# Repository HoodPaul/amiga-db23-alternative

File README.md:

# Amiga DB23 Video and Floppy Adapter

An adapter assembly for the Amiga's motherboard-mounted **DB23 RGB video and external floppy connectors**. A genuine solder-cup DB23 joins a small horizontal PCB, 23 supported straight pins and a solid printed base. Two screws clamp the assembly through the original motherboard mounting holes, with nuts above the adapter PCB and insulating washers under the motherboard-side heads. An optional cosmetic cover locates on the front towers and can be secured with tiny glue spots. **Mechanical/assembly revision: 0.6. PCB revision: 0.5.**

Project development: **Paul of UK Computing Limited**, **Jon of JMC Electronics** and **AI assistance through Codex**. This develops Paul's supplied straddle-PCB concept and supported loose-pin construction.

Repository: [HoodPaul/amiga-db23-alternative](https://github.com/HoodPaul/amiga-db23-alternative).

**Status, 30 October 2026: fit prototype. Paul has trial-printed revision 0.5 and reported delicate lid projections and nuts contained within the print footprint. The revised 0.6 parts have not yet been printed. The complete connector, fastener and PCB stack remains unmeasured. No physical strength, assembled electrical operation or Amiga compatibility test has been completed.** Native files and trial prints make those checks possible; this is not a production release.

For engineering or AI work, read [AGENTS.md](AGENTS.md), the [handover](docs/AI-HANDOVER.md) and [documentation index](docs/README.md).

The printed geometry comes from the delivered CAD. Bought connector bodies, cups, pins and hardware are unmeasured reference envelopes. Their appearance does not prove a purchased part fits. See the [drawing PDF](previews/DB23_Prototype_Drawings_v0.6.pdf) for fit references and assembly views.

## Revision 0.6 mechanical arrangement

The DB23 cups straddle the front of the PCB: contacts 1–12 solder to the top and 13–23 to the bottom. Twenty-three separate pins pass through the base into the original motherboard signal holes.

The PCB has side ears with plated `SHIELD` mounting lands at the original shell-anchor positions. **M3 screws enter from underneath the motherboard**, pass through the solid base and PCB, and take nuts on top, with insulating washers beneath the screw heads. The printed base has one broad, flat underside at motherboard Z0 and supports the PCB at Z5.75.

The forward towers have straight, square outer faces at X±25.60. Clearance for neighbouring components starts behind the towers.

Dedicated J4 shell-bond pads keep wire and solder away from the J3 nut-bearing lands. The cap fits last, after mounting and inspection. It provides the discreet black appearance; fitted jackposts must retain their nuts with the cover absent. The solid base and through-bolts carry the intended cable loads. Actual insertion strength and clamping behaviour remain untested.

The build order follows four parts: **join DB23 and PCB; load pins with the separate height jig and solder the joined assembly onto them; fit jackpost nuts and posts; mount and solder to the motherboard, inspect, then fit the cap.** See the [assembly guide](docs/ASSEMBLY.md).

## PCB variants

Open the matching project with **KiCad 7.0 or newer**:

| Variant | Native project | Connector on the Amiga |
|---|---|---|
| RGB video | [DB23M_RGB.kicad_pro](pcb/DB23M_RGB/DB23M_RGB.kicad_pro) | Male DB23 solder-cup connector |
| External floppy | [DB23F_Floppy.kicad_pro](pcb/DB23F_Floppy/DB23F_Floppy.kicad_pro) | Female DB23 solder-cup connector |

Local symbols and footprints are included. Male and female pin numbering is mirrored; use the matching PCB.

| PCB property | Revision 0.5 |
|---|---|
| Overall board envelope | **51.20 × 9.00 mm**, Y4.00–13.00, with mounting ears, front clearance steps and local reliefs |
| Layers / assumed thickness | **Two / 1.00 mm**; confirm the actual cup gap |
| Proposed finish | Black mask, white silkscreen, ENIG exposed pads |
| PCB legend, both faces | **Amiga DB23 REV 0.5**, nominal 0.70 mm text height / 0.10 mm stroke |
| Signal track / clearance | **0.50 / 0.20 mm** |
| Tail drill / pad | **1.04 / 1.70 mm** |
| J3 mounting drill / pad | **3.30 / 6.50 mm** |
| J4 shell-wire drill / pad | **1.20 / 2.40 mm** |
| Along-row pitch / spacing / stagger | **2.77 / 2.84 / 1.385 mm** |
| Front / rear signal rows | **Y8.08 / Y10.92 mm** from flange datum |
| Shell mounting centres | **44.27 mm**, at **Y9.50 mm** |
| Nominal mating centreline | **6.25 mm** above the motherboard |

The hole pattern and mating references are nominal values from the [iComp OEM-equivalent drawings](docs/SOURCES.md). The PCB rear is now Y13.00 rather than Y16.00, 3.00 mm shorter than revision 0.4. The cap reaches Y13.20, 0.70 mm behind the OEM reference rear at Y12.50. The prints are 52.00 mm wide, but the pair of Ø8 underside washers spans 52.27 mm. Actual side-exiting wire and case/component clearance still need checking on the target motherboard.

## Printed parts and mounting hardware

The [mechanical folder](mechanical/) contains editable OpenSCAD and the following trial parts:

- [Solid base STL](mechanical/DB23_Holder_v0.6.stl) and [STEP](mechanical/DB23_Holder_v0.6.step).
- [Optional cover STL](mechanical/DB23_Cap_v0.6.stl) and [STEP](mechanical/DB23_Cap_v0.6.step).
- [Pin-height jig](mechanical/DB23_Pin_Height_Jig_v0.6.stl) and [hole-fit coupon](mechanical/DB23_Hole_Fit_Coupon_v0.6.stl).

Read [mechanical notes](docs/MECHANICAL.md) and `mechanical/MECHANICAL_NOTES.txt` for orientations and fit allowances. The cap STL is already roof-down for printing; its STEP uses assembly coordinates. The base has a broad, flat Z0 underside for direct bed placement, subject to the usual first-layer and dimensional trial.

All 23 guides now have **0.40 mm deep, 45° entry funnels**, opening to **Ø1.72 mm** at the surface. This is two layers at 0.20 mm layer height, with the straight retaining bore preserved below. The cover has a **1.60 mm roof**, a short **1.20 mm rim**, and two broad locating tabs. The four thin projections, two hooks and their base catches are removed; obsolete clip coupons are removed too.

The default guides are nominally **Ø0.92 mm** for assumed **0.64 mm square pins**. Their diagonal is about **0.905 mm**, so a finished Ø0.80 mm round bore is too small. Establish snug pin retention using the coupon and actual pins. Use the funnel to guide careful hand clearing with a pin vice if needed. Hot insertion is unvalidated and can move or soften the guide. The loading jig sets a common lower-tip stop; equal upper heights also need equal pin lengths. Remove the jig before soldering.

The default motherboard fastener is **M3 × 12 mm under-head length**, with a user-listed **Ø7 mm, approximately 1 mm thick head**. Fit a **Ø8 mm insulating washer, assumed 0.50 mm thick, beneath each head**; the top nut bears directly on its supported J3 land. With an assumed 1.60 mm motherboard and 2.40 mm nut, the stack takes 11.25 mm, leaving 0.75 mm beyond the nut. The screw tip is Z9.90 and the head bottom Z−3.10, 1.50 mm beneath the assumed motherboard underside. Measure the real stack and underside/chassis clearance. **14 and 16 mm screws require trimming or separately checked cap clearance.** A top washer is not part of the default stack and needs a separate length check. No motherboard countersinking or drilling is specified.

Port jackposts need **4-40 UNC cable-facing threads** and rear stems matching the captive nuts. Prototype defaults use M3 rear stems and nuts. The clearance passage ends at Y6.20; the conservative permitted stem end is **Y≤6.00 from the flange datum**, before the upward mounting nuts. Select the actual hardware before freezing the print.

## Electrical arrangement and validation

All **23 positions pass independently, pin n to pin n**, using neutral `P01`–`P23` names. The bare PCB keeps `SHIELD` separate from every signal pin, including video pin 13. It adds no buffering, conversion, protection or change to the Amiga interface.

J3 mounting lands and J4 shell-wire pads share `SHIELD`. Provide deliberate wires or metal bonds from the DB23 shell and from J4 to the original motherboard shell-ground pad. The default head washers are insulating, and mounting-bolt contact is not relied upon for motherboard grounding. Plastic provides no grounding.

Use the [current validation record](docs/VALIDATION.md) for actual native DRC, exact-netlist and independent geometry results. Native schematic ERC is not claimed. CAD checks do not establish physical fit, printed strength, heat tolerance or working hardware.

Run the portable PCB audit from the project root:

```sh
python3 source/verify_pcb.py
```

Complete the [measurements](docs/MEASUREMENTS.md) and trial prints before a board order. Generated files under [fabrication/FIT-PROTOTYPE/](fabrication/FIT-PROTOTYPE/) are coordinated prototype exports, not a measured production release.

## Project contents

| Path | Purpose |
|---|---|
| [pcb/](pcb/) | Both KiCad projects and local libraries |
| [mechanical/](mechanical/) | Editable source, print trials and STEP geometry |
| [previews/](previews/) | Assembly, print and PCB views, drawing PDF |
| [docs/](docs/) | Assembly, measurements, design decisions and handover |
| [source/](source/) | Shared parameters, builders and verifiers |
| [verification/](verification/) | Actual native and saved-file reports |
| [BOM.csv](BOM.csv) | Parts and selection assumptions |
| [CHANGELOG.md](CHANGELOG.md) | Revision history |
| [NOTICE.md](NOTICE.md) | Project and third-party notices |

## Universal PCB prototype — ordered 30 October 2026

**Use the universal PCB at your own risk.** A separate [universal prototype package](pcb/DB23_Universal_Prototype/README.md) now includes editable PCB, Gerbers/drills, preview, checks and order records. It retains the existing physical routing, adds VIDEO 1 / FLOPPY 1 markings on both faces, removes other numbers and uses round signal pads. Internal numbering remains the VIDEO reference; actual connector orientation and continuity must be checked.

Paul confirmed ordering 30 boards from JLCPCB on 30 October 2026: two-layer FR-4, 1.00 mm, 1 oz, black mask, white silkscreen, ENIG. Receipt, physical fit and functional operation remain unverified. Native KiCad 10.0.7 DRC reports zero errors/unconnected items and four missing-library warnings; exact checks confirm 23 separate signal connections. This is a standalone board snapshot, not a new coordinated PCB revision or a replacement for the two existing variants.

### Hardware order update — 30 October 2026

Paul confirmed **30 PCBs** (correcting the earlier 20), **100 M3 × 12 mm screws with 7 mm heads**, **100 M3 304 stainless nuts**, and **40 strips of 1×40 L11.5 headers** (nominally 1,600 pins). See [the order details](pcb/DB23_Universal_Prototype/ORDER_RECORD_2026-10-30.md). The selected 11.5 mm pins are intended to be used untrimmed after carrier removal; nominal protrusion above the PCB is 1.55 mm and roof clearance 2.70 mm with the existing jig. Actual dimensions and fit are unverified; main CAD still models 10.70 mm pins. Earlier quoted prices apply to the original 20-board screenshot, not the final 30-board order.

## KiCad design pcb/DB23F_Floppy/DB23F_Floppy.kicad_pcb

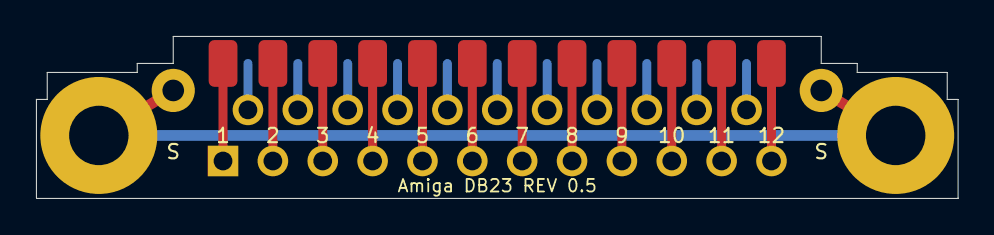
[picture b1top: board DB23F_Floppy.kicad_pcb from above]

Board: 2 copper layers, 51.2 x 9.0 mm, 4 parts (0 on the bottom side), 24 nets.

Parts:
J1: DB23F solder cups; Cups23_F
J2: Pins to motherboard; Motherboard23_F
J3: M3 mounting / shield; MountingShield_F
J4: DB23 shell wire bond; ShellBond_F

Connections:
/P01: J1.1, J2.1
/P02: J1.2, J2.2
/P03: J1.3, J2.3
/P04: J1.4, J2.4
/P05: J1.5, J2.5
/P06: J1.6, J2.6
/P07: J1.7, J2.7
/P08: J1.8, J2.8
/P09: J1.9, J2.9
/P10: J1.10, J2.10
/P11: J1.11, J2.11
/P12: J1.12, J2.12
/P13: J1.13, J2.13
/P14: J1.14, J2.14
/P15: J1.15, J2.15
/P16: J1.16, J2.16
/P17: J1.17, J2.17
/P18: J1.18, J2.18
/P19: J1.19, J2.19
/P20: J1.20, J2.20
/P21: J1.21, J2.21
/P22: J1.22, J2.22
/P23: J1.23, J2.23
/SHIELD: J3.1, J3.2, J4.1, J4.2

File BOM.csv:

Reference,Quantity,Description,Specification,Selection status,Notes
J1,1,DB23 solder-cup connector,Male for RGB or female for floppy,Part not selected,"Measure rear body, cup gap/length, flange and mounting clearances before freezing CAD"
PCB,1,DB23 adapter PCB,Revision 0.5; matching variant; overall 51.20 x 9.00 mm; two layers; 1.00 mm assumed,Fit prototype,J3 mounting lands at original shell anchors; dedicated J4 shell-wire pads
P01-P23,23,Straight motherboard pins,0.64 mm square assumed; 10.70 mm equal overall lengths,Actual pins not measured,May recover suitable long pins from 0.1-inch header stock after removing its carrier; determine finished guide fit by coupon
H1,1,Solid printed base,DB23_Holder_v0.5.stl,Trial print,Integral mounting feet replace old loose shims; supports PCB ears and all 23 pins
H2,1,Keyed clip-on cap,DB23_Cap_v0.5.stl,Trial print,Black proposed; retains jackpost nuts and covers top hardware; fit last; latch strength and release untested
N1-N2,2,Captive port-jackpost nuts,M3 prototype default; AF5.50 x 2.40 mm assumed,Part not frozen,Match actual rear stems; do not assume M3.5
JS1-JS2,2,Hex port jackposts,4-40 UNC cable-facing socket; M3 rear stem candidate,Part not frozen,Permitted rear stem end Y<=6.00 from flange datum; passage ends Y6.20; check actual nuts and mounting hardware
MB1-MB2,2,Upward motherboard mounting screws,M3 x 12 mm under-head length; head diameter 7 mm and thickness about 1 mm,User listing; unmeasured,"Pass upward through underside insulating washer, original motherboard holes, base and J3; verify nominal head bottom Z-3.10 against chassis; no drilling/countersinking"
MB-IW1-MB-IW2,2,Under-head insulating washers,OD8.00 / ID3.20 x thickness0.50 mm assumed,Required default; actual part not measured,Fit between screw heads and motherboard underside; verify nearby copper and chassis space; no reliance on bolt grounding
MB-N1-MB-N2,2,Top mounting nuts,M3; AF5.50 x height2.40 mm assumed,Part not frozen,Seat directly on supported J3 lands with no default top washer; check full thread engagement and cap clearance
SH1-SH2,As required,Shell-ground bonds,Short insulated wire or suitable metal strap to J4,Assembly design to confirm,Bond DB23 shell and original motherboard shell-ground pad deliberately to J4; route board bond through base foot groove; do not rely on bolt contact
CP1,1,Hole-fit coupon,DB23_Hole_Fit_Coupon_v0.5.stl,Trial tool only,Print and test actual pins before the full base; not installed
JIG1,1,Pin-height loading jig,DB23_Pin_Height_Jig_v0.5.stl,Loading tool only,Supports integrated feet and common lower-tip stop; remove before soldering
FB1-FB2,As required,Flange bearing spacers,Thickness selected from actual flange-to-base gap,Fit-dependent,Nominal reference gap0.15 mm is not a fixed required spacer; establish bearing without bending cups or tails
CP2-CP3,1 matched pair,Clip-fit coupons,DB23_Clip_Fit_Base_v0.5.stl and DB23_Clip_Fit_Cap_v0.5.stl,Trial tools only,Validate latch engagement/release and printer/material behaviour before full cap; not installed
CS1-CS2,Optional; if developed,Rigid compression stops,Match actual support height and selected base bore,Not a frozen drop-in part,Consider only with reviewed matching hardware/base; do not crush print or bow PCB
